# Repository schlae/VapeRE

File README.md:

# Reverse Engineered Vape Circuit Boards

Disposable vapes show up all the time in e-waste and are often found as litter at the side of the road (shame!) but they contain some useful components that can be reused by the cost-conscious hacker.

*Note: Wear gloves when handling used devices and don't allow the vape liquid to contact your skin or eyes.*

I've reverse engineered a number of different brands and placed the schematics and layout files in this repository. The summary table below is a good starting point.

Many of the vapes have debugging connections accessible through the USB-C charging cable interface, typically SWD on the CC pins, so you may be able to reprogram the vape without even opening up the case.

| Brand | PCB ID | Display | MCU | NOR flash | Battery IC | LDO regulator | Debug | Other Notes |
|-------|--------|---------|-----|-----------|------------|---------------|-------|-------------|
| (Unknown) | [FT03 V3.0](FT03/) | LCD | CHIPSEA F031K8V6 | GT 25Q32A | PC3221 | CJ6330 | SWD on CC lines. UART test points. | Touch IC TTP223. Pushbutton. 3 heater outputs with feedback. |
| Flum Mello | [TMY\_0118470101\_V04](TMY/) | LCD | CHIPSEA F031K8V6 | ZB 25VQ32 | TP4054 | CJ6330 | SWD on CC lines. | One heater output with feedback. |
| Rama 16000 | [YK761-VP9012-A](YK761/) | LCD | BlueX BX2400 or RF01 | Puya PY25Q64 | CST4056 | CJ6330 | Test points for SWD | One heater with feedback. Bluetooth (!) |
| GeekBar Pulse 15000 | [BD0027-USB\_V1.5](BD0027/) | Blue and RGB LEDs | Puya PY32F030EK28 | None | LP4068 | None | SWD on CC lines. | 3-position slide switch. Two heaters with feedback. |
| Lost Mary MO20000 Pro | [STW2915 V1.7](STW2915/) | LCD | Pya PY32F030EK28 | Puya PY32Q64 | LP4068 | CJ6330 (?) | SWD on CC lines. | |
| GeekBar Pulse X Jam | [BD0061](BD0061/) | LCD and blue LEDs, PLS916H driver IC | Puya PY32F030EK28 | None | LR5112/LR5108 | None | SWD on CC lines. | |

I also have [firmware running on the Lost Mary MO20000 Pro](STW2915/firmware) that could be modified to run on other vapes with the same PY32F030 microcontroller.

## License

All the reverse engineered hardware data is provided under the [Creative Commons Attribution-ShareAlike 4.0 International](https://creativecommons.org/licenses/by-sa/4.0/) license.

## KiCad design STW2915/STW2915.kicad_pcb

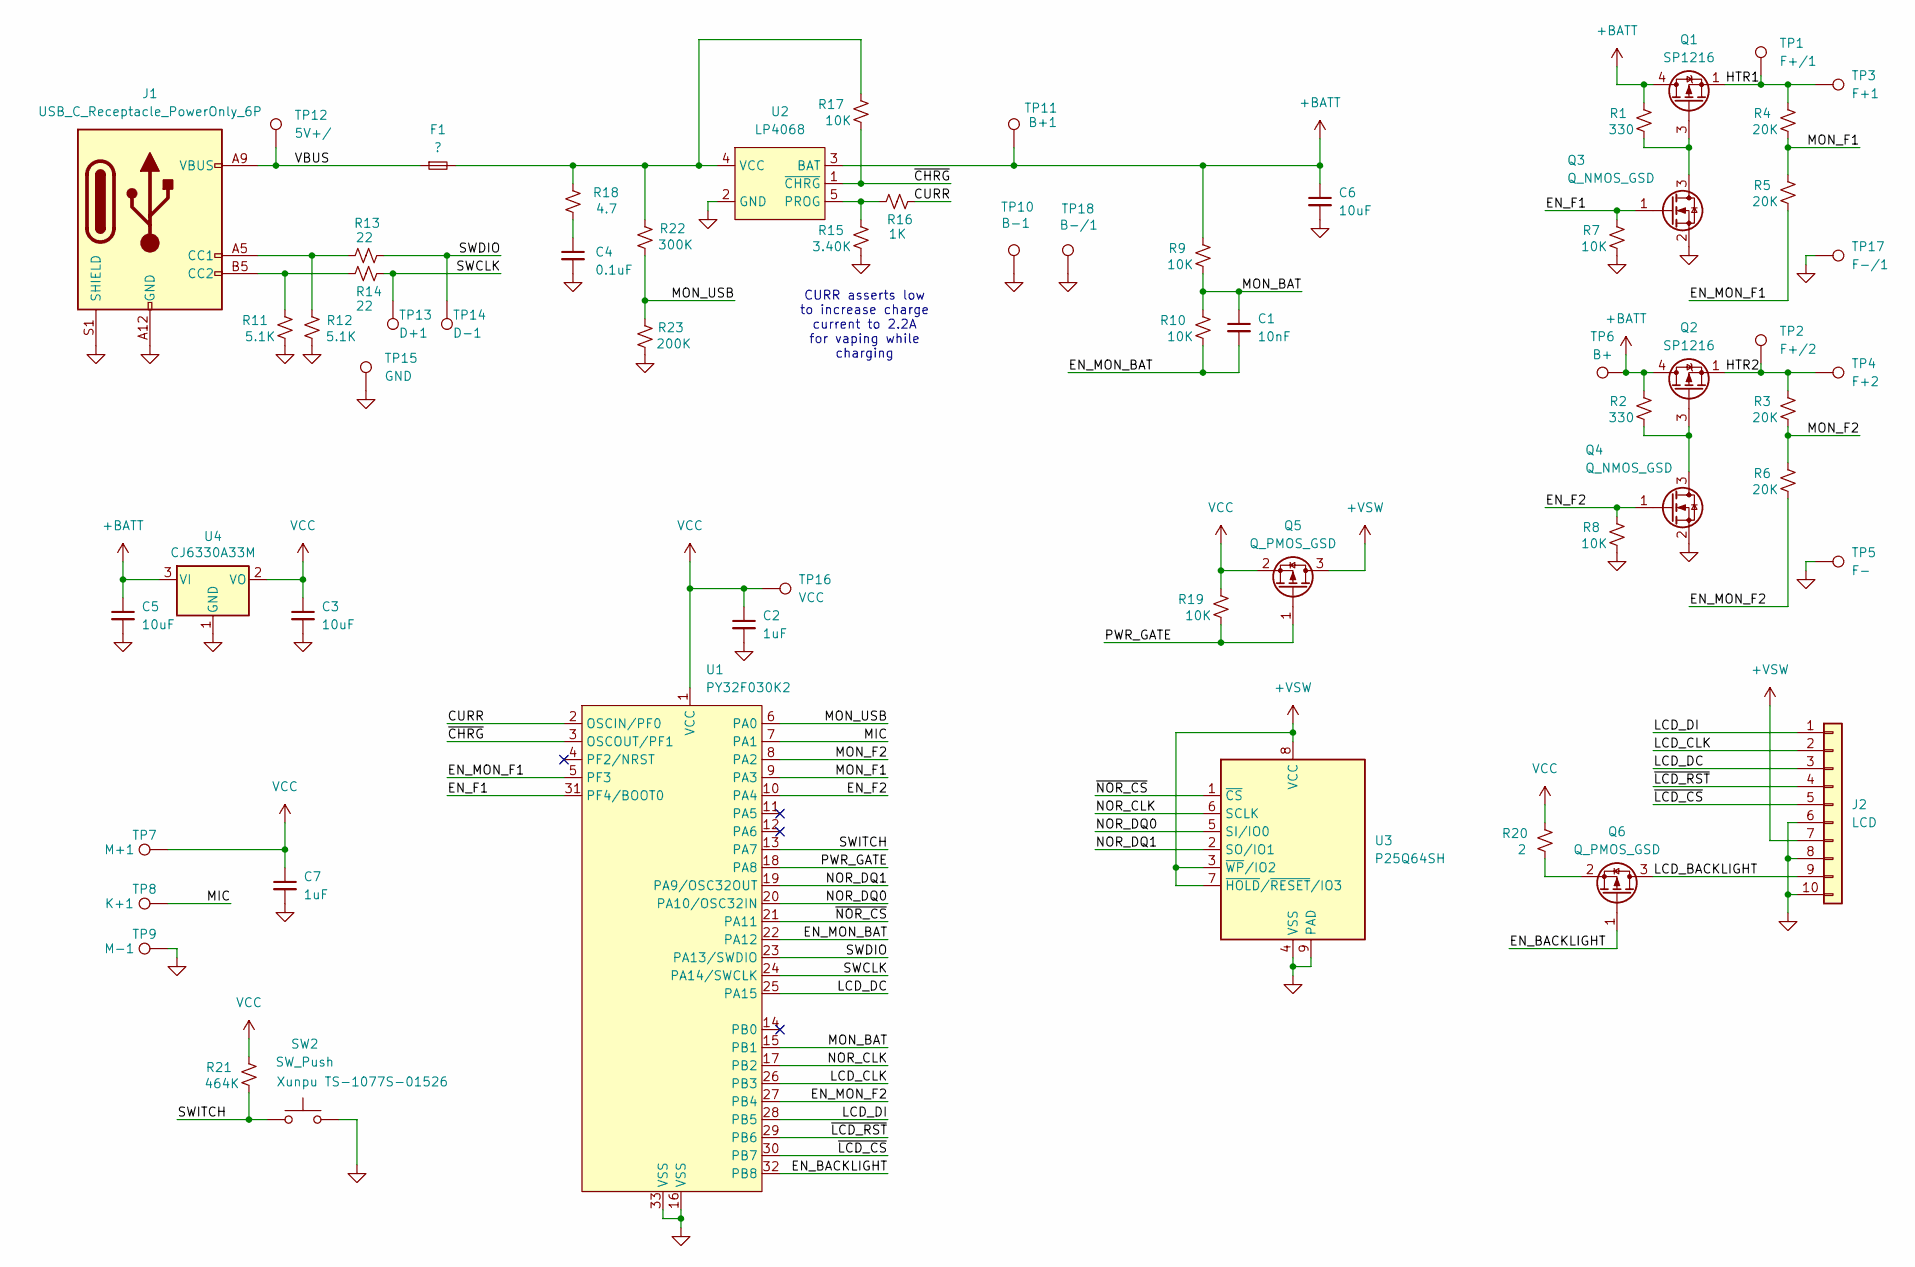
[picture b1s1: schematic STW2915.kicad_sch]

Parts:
C1: 10nF; C_0402_1005Metric
C2, C7: 1uF; C_0402_1005Metric
C3, C5, C6: 10uF; C_0402_1005Metric
C4: 0.1uF; C_0402_1005Metric
F1: ?; Fuse_0603_1608Metric
J1: USB_C_Receptacle_PowerOnly_6P; USB_C_Receptacle_TYPE-C-VERT
J2: LCD; FPC_CONN_1_2MM-10
Q1, Q2: SP1216; Texas_DQK
Q3, Q4: Q_NMOS_GSD; SOT-523
Q5, Q6: Q_PMOS_GSD; SOT-723
R1, R2: 330; R_0402_1005Metric
R3, R4, R5, R6: 20K; R_0402_1005Metric
R7, R8, R9, R10, R17, R19: 10K; R_0402_1005Metric
R11, R12: 5.1K; R_0402_1005Metric
R13, R14: 22; R_0402_1005Metric
R15: 3.40K; R_0402_1005Metric
R16: 1K; R_0402_1005Metric
R18: 4.7; R_0402_1005Metric
R20: 2; R_0402_1005Metric
R21: 464K; R_0402_1005Metric
R22: 300K; R_0402_1005Metric
R23: 200K; R_0402_1005Metric
SW2: SW_Push; SW_Push_1P1T_NO_CK_KMR2; MPN Xunpu TS-1077S-01526
TP1: F+/1; TestPoint_Pad_D1.0mm
TP2: F+/2; TestPoint_Pad_D1.0mm
TP3: F+1; TestPoint_Pad_D1.5mm
TP4: F+2; TestPoint_Pad_D1.5mm
TP5: F-; TestPoint_Pad_D1.5mm
TP6: B+; TestPoint_Pad_D1.5mm
TP7: M+1; TestPoint_Pad_D1.5mm
TP8: K+1; TestPoint_Pad_D1.5mm
TP9: M-1; TestPoint_Pad_D1.5mm
TP10: B-1; TestPoint_Pad_D1.5mm
TP11: B+1; TestPoint_Pad_D1.5mm
TP12: 5V+/; TestPoint_Pad_D1.0mm
TP13: D+1; TestPoint_Pad_D1.0mm
TP14: D-1; TestPoint_Pad_D1.0mm
TP15: GND; TestPoint_Pad_D1.0mm
TP16: VCC; TestPoint_Pad_D1.0mm
TP17: F-/1; TestPoint_Pad_D1.5mm
TP18: B-/1; TestPoint_Pad_D1.5mm
U1: PY32F030K2; QFN-32-1EP_5x5mm_P0.5mm_EP3.45x3.45mm
U2: LP4068; TSOP-5_1.65x3.05mm_P0.95mm
U3: P25Q64SH; Winbond_USON-8-1EP_3x2mm_P0.5mm_EP0.2x1.6mm
U4: CJ6330A33M; SOT95P230X117-3

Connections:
+3.3V: J2.7, Q5.3 (D), U3.3 (~WP/IO2), U3.7 (~HOLD/~RESET/IO3), U3.8 (VCC)
+BATT: C5.1, C6.1, Q1.4 (D), Q1.7 (D), Q2.4 (D), Q2.7 (D), R1.2, R2.2, R9.2, TP6.1, TP11.1, U2.3 (BAT), U4.3 (VI)
/CURR: R16.1, U1.2 (OSCIN/PF0)
/EN_BACKLIGHT: Q6.1 (G), U1.32 (PB8)
/EN_F1: Q3.1 (G), R7.2, U1.31 (PF4/BOOT0)
/EN_F2: Q4.1 (G), R8.2, U1.10 (PA4)
/EN_MON_BAT: C1.2, R10.1, U1.22 (PA12)
/EN_MON_F1: R5.1, U1.5 (PF3)
/EN_MON_F2: R6.1, U1.27 (PB4)
/HTR1: Q1.1 (S), Q1.2 (S), Q1.5 (S), Q1.6 (S), Q1.8 (S), R4.2, TP1.1, TP3.1
/HTR2: Q2.1 (S), Q2.2 (S), Q2.5 (S), Q2.6 (S), Q2.8 (S), R3.2, TP2.1, TP4.1
/LCD_BACKLIGHT: J2.9, Q6.3 (D)
/LCD_CLK: J2.2, U1.26 (PB3)
/LCD_DC: J2.3, U1.25 (PA15)
/LCD_DI: J2.1, U1.28 (PB5)
/MIC: TP8.1, U1.7 (PA1)
/MON_BAT: C1.1, R9.1, R10.2, U1.15 (PB1)
/MON_F1: R4.1, R5.2, U1.9 (PA3)
/MON_F2: R3.1, R6.2, U1.8 (PA2)
/MON_USB: R22.1, R23.2, U1.6 (PA0)
/NOR_CLK: U1.17 (PB2), U3.6 (SCLK)
/NOR_DQ0: U1.20 (PA10/OSC32IN), U3.5 (SI/IO0)
/NOR_DQ1: U1.19 (PA9/OSC32OUT), U3.2 (SO/IO1)
/PWR_GATE: Q5.1 (G), R19.1, U1.18 (PA8)
/SWCLK: R14.1, TP13.1, U1.24 (PA14/SWCLK)
/SWDIO: R13.1, TP14.1, U1.23 (PA13/SWDIO)
/SWITCH: R21.1, SW2.1, U1.13 (PA7)
/VBUS: F1.1, J1.A9 (VBUS), J1.B9 (VBUS), TP12.1
/~CHRG: R17.1, U1.3 (OSCOUT/PF1), U2.1 (~CHRG)
/~LCD_CS: J2.5, U1.30 (PB7)
/~LCD_RST: J2.4, U1.29 (PB6)
/~NOR_CS: U1.21 (PA11), U3.1 (~CS)
GND: C2.2, C3.2, C4.2, C5.2, C6.2, C7.2, J1.A12 (GND), J1.B12 (GND), J1.S1 (SHIELD), J2.6, J2.8, J2.10, Q3.2 (S), Q4.2 (S), R7.1, R8.1, R11.1, R12.1, R15.1, R23.1, SW2.2, TP5.1, TP9.1, TP10.1, TP15.1, TP17.1, TP18.1, U1.16 (VSS), U1.33 (VSS), U2.2 (GND), U3.4 (VSS), U3.9 (PAD), U4.1 (GND)
unnamed: C4.1, R18.1
unnamed: J1.A5 (CC1), R12.2, R13.2
unnamed: J1.B5 (CC2), R11.2, R14.2
unnamed: Q1.3 (G), Q3.3 (D), R1.1
unnamed: Q2.3 (G), Q4.3 (D), R2.1
unnamed: Q6.2 (S), R20.1
unnamed: R15.2, R16.2, U2.5 (PROG)
unnamed: F1.2, R17.2, R18.2, R22.2, U2.4 (VCC)
VCC: C2.1, C3.1, C7.1, Q5.2 (S), R19.2, R20.2, R21.2, TP7.1, TP16.1, U1.1 (VCC), U4.2 (VO)

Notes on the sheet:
CURR asserts low to increase charge current to 2.2A for vaping while charging

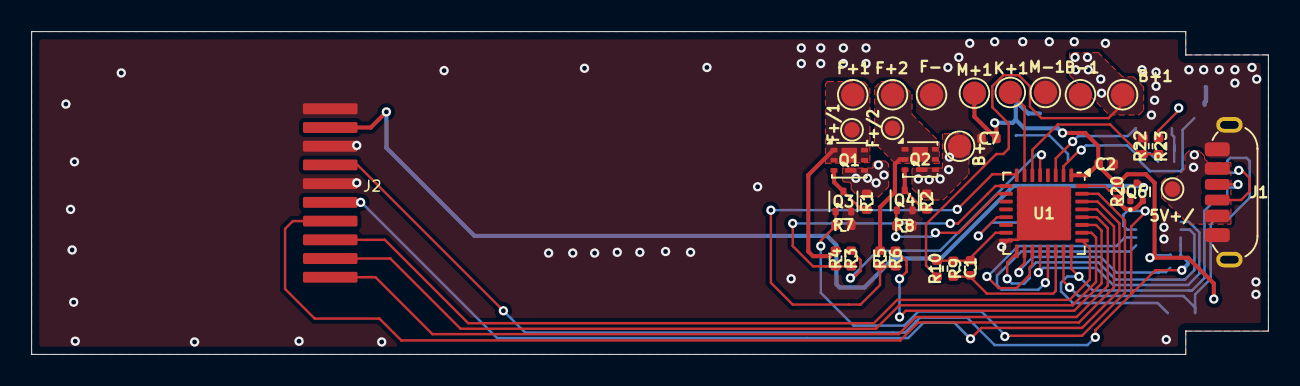
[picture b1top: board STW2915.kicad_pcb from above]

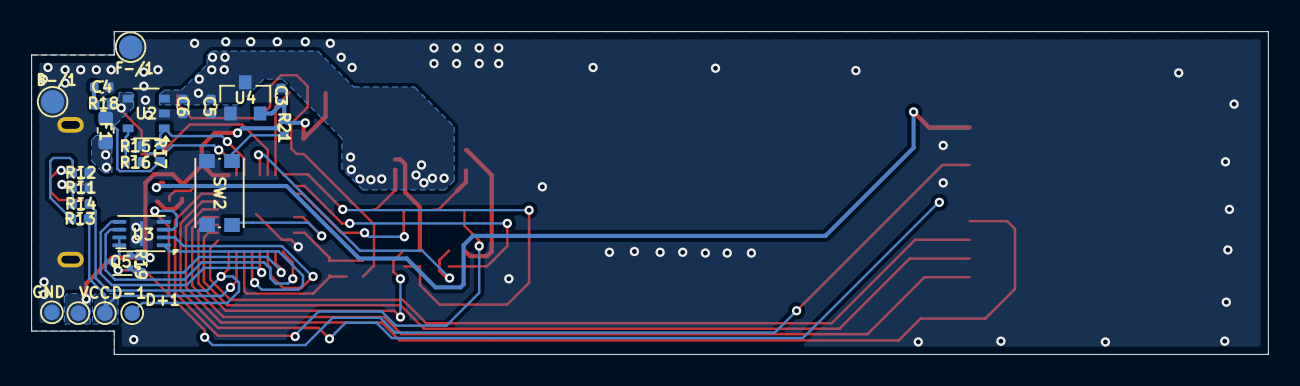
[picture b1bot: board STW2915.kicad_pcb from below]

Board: 2 copper layers, 79.3 x 20.7 mm, 62 parts (26 on the bottom side), 42 nets.

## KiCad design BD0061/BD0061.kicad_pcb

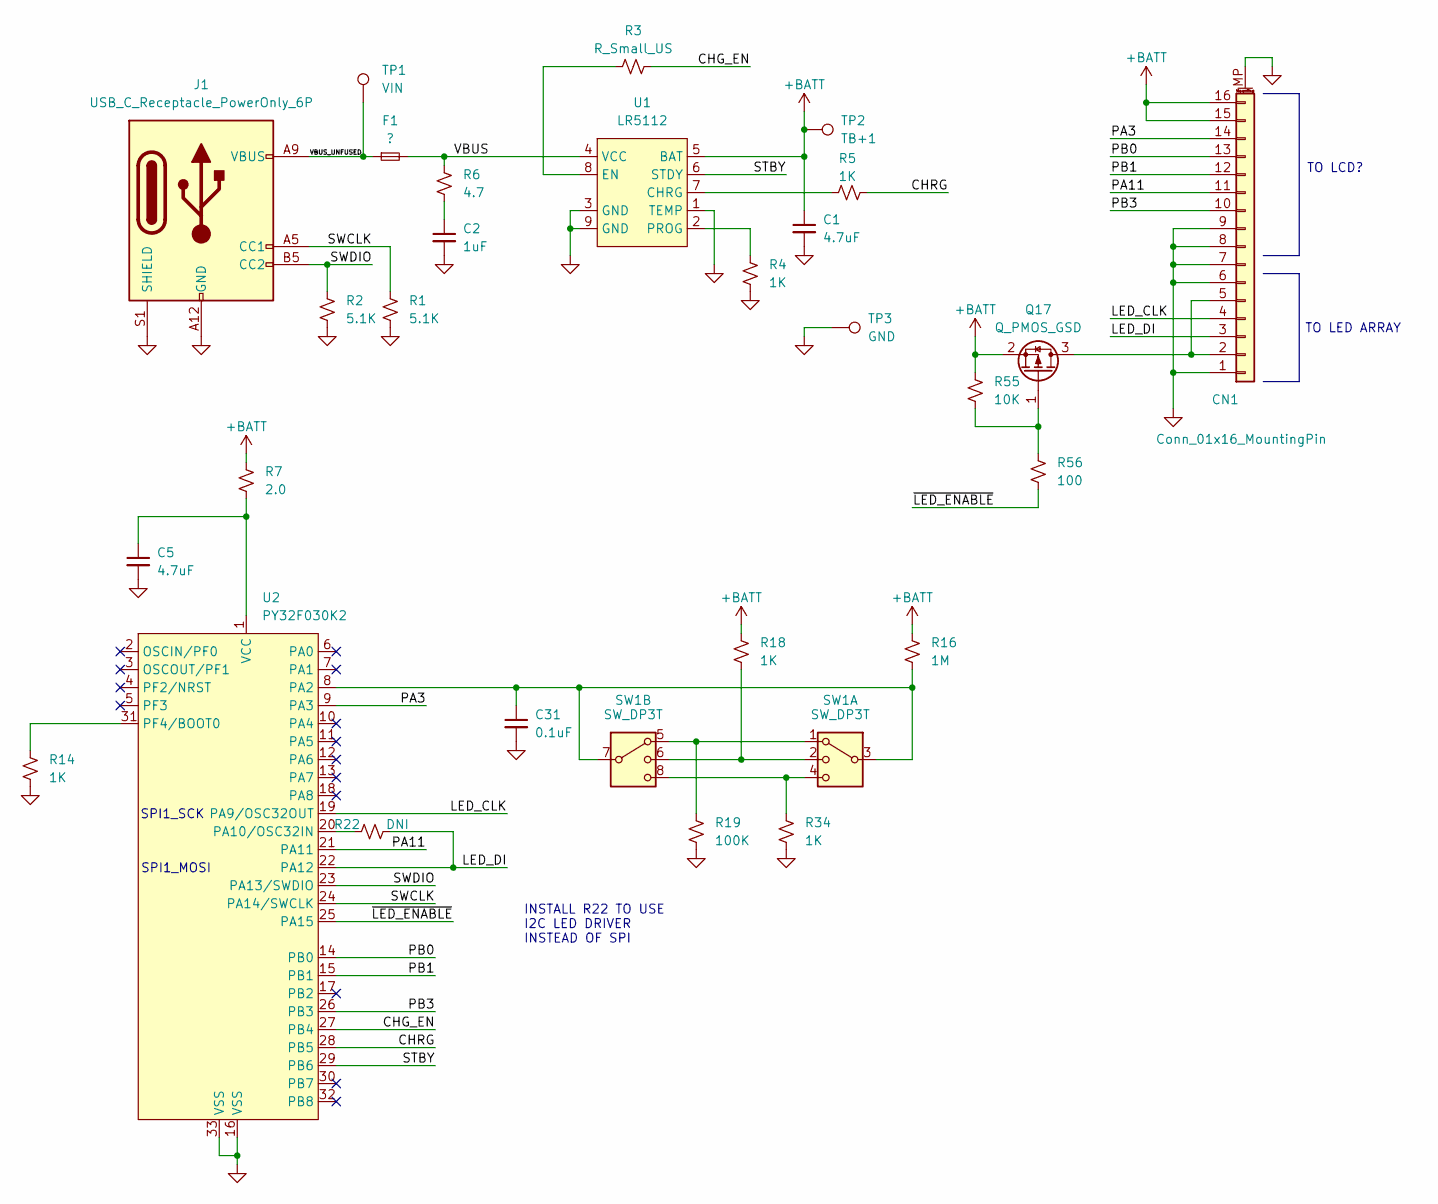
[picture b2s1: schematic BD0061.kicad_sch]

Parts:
C1: 4.7uF; C_0603_1608Metric
C2: 1uF; C_0603_1608Metric
C5: 4.7uF; C_0402_1005Metric
C31: 0.1uF; C_0402_1005Metric
CN1: Conn_01x16_MountingPin; UNK_FPC_1x16-1MP_P0.5mm_Horizontal
F1: ?; Fuse_0603_1608Metric
J1: USB_C_Receptacle_PowerOnly_6P; USB_C_Receptacle_TYPE-C-VERT
Q17: Q_PMOS_GSD; SOT-523
R1, R2: 5.1K; R_0402_1005Metric
R3: R_Small_US; R_0402_1005Metric
R4, R5, R14, R18, R34: 1K; R_0402_1005Metric
R6: 4.7; R_0402_1005Metric
R7: 2.0; R_0402_1005Metric
R16: 1M; R_0402_1005Metric
R19: 100K; R_0402_1005Metric
R22: DNI; R_0402_1005Metric
R55: 10K; R_0402_1005Metric
R56: 100; R_0402_1005Metric
SW1: SW_DP3T; SW_DP3T_SMD
TP1: VIN; TestPoint_Pad_D1.5mm
TP2: TB+1; TestPoint_Pad_D1.5mm
TP3: GND; TestPoint_Pad_D1.5mm
U1: LR5112; DFN-8-1EP_3x3mm_P0.65mm_EP1.55x2.4mm
U2: PY32F030K2; QFN-32-1EP_5x5mm_P0.5mm_EP3.45x3.45mm

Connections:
+BATT: C1.1, CN1.15, CN1.16, Q17.2 (S), R7.1, R16.2, R18.2, R55.2, TP2.1, U1.5 (BAT)
/CHG_EN: R3.2, U2.27 (PB4)
/CHRG: R5.2, U2.28 (PB5)
/PA3: CN1.14, U2.9 (PA3)
/PA9: CN1.4, U2.19 (PA9/OSC32OUT)
/PA11: CN1.11, U2.21 (PA11)
/PA12: CN1.3, R22.1, U2.22 (PA12)
/PB0: CN1.13, U2.14 (PB0)
/PB1: CN1.12, U2.15 (PB1)
/PB3: CN1.10, U2.26 (PB3)
/STBY: U1.6 (STDY), U2.29 (PB6)
/SWCLK: J1.A5 (CC1), R1.1, U2.24 (PA14/SWCLK)
/SWDIO: J1.B5 (CC2), R2.1, U2.23 (PA13/SWDIO)
/VBUS: F1.2, R6.2, U1.4 (VCC)
/VBUS_UNFUSED: F1.1, J1.A9 (VBUS), J1.B9 (VBUS), TP1.1
/~LCD_BACKLIGHT: R56.2, U2.25 (PA15)
GND: C1.2, C2.2, C5.2, C31.2, CN1.1, CN1.6, CN1.7, CN1.8, CN1.9, CN1.MP (MountPin), J1.A12 (GND), J1.B12 (GND), J1.S1 (SHIELD), R1.2, R2.2, R4.2, R14.2, R19.2, R34.2, TP3.1, U1.1 (TEMP), U1.3 (GND), U1.9 (GND), U2.16 (VSS), U2.33 (VSS)
unnamed: C2.1, R6.1
unnamed: CN1.2, CN1.5, Q17.3 (D)
unnamed: Q17.1 (G), R55.1, R56.1
unnamed: R18.1, SW1.2, SW1.6
unnamed: R19.1, SW1.1, SW1.5
unnamed: R34.1, SW1.4, SW1.8
unnamed: R5.1, U1.7 (CHRG)
unnamed: R3.1, U1.8 (EN)
unnamed: R4.1, U1.2 (PROG)
unnamed: C31.1, R16.1, SW1.3, SW1.7, U2.8 (PA2)
unnamed: R22.2, U2.20 (PA10/OSC32IN)
unnamed: R14.1, U2.31 (PF4/BOOT0)
unnamed: C5.1, R7.2, U2.1 (VCC)

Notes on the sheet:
SPI1_SCK
INSTALL R22 TO USE I2C LED DRIVER INSTEAD OF SPI
TO LED ARRAY
TO LCD?
SPI1_MOSI

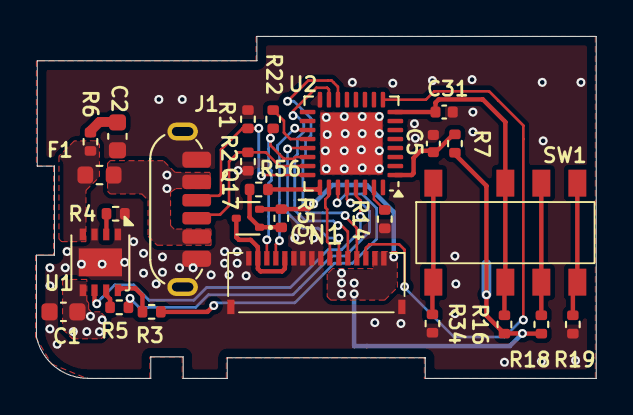
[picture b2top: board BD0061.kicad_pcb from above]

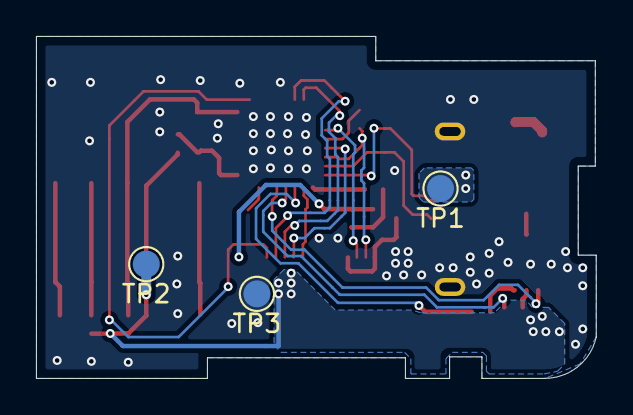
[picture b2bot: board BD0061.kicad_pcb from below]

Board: 2 copper layers, 31.1 x 19.0 mm, 29 parts (3 on the bottom side), 30 nets.

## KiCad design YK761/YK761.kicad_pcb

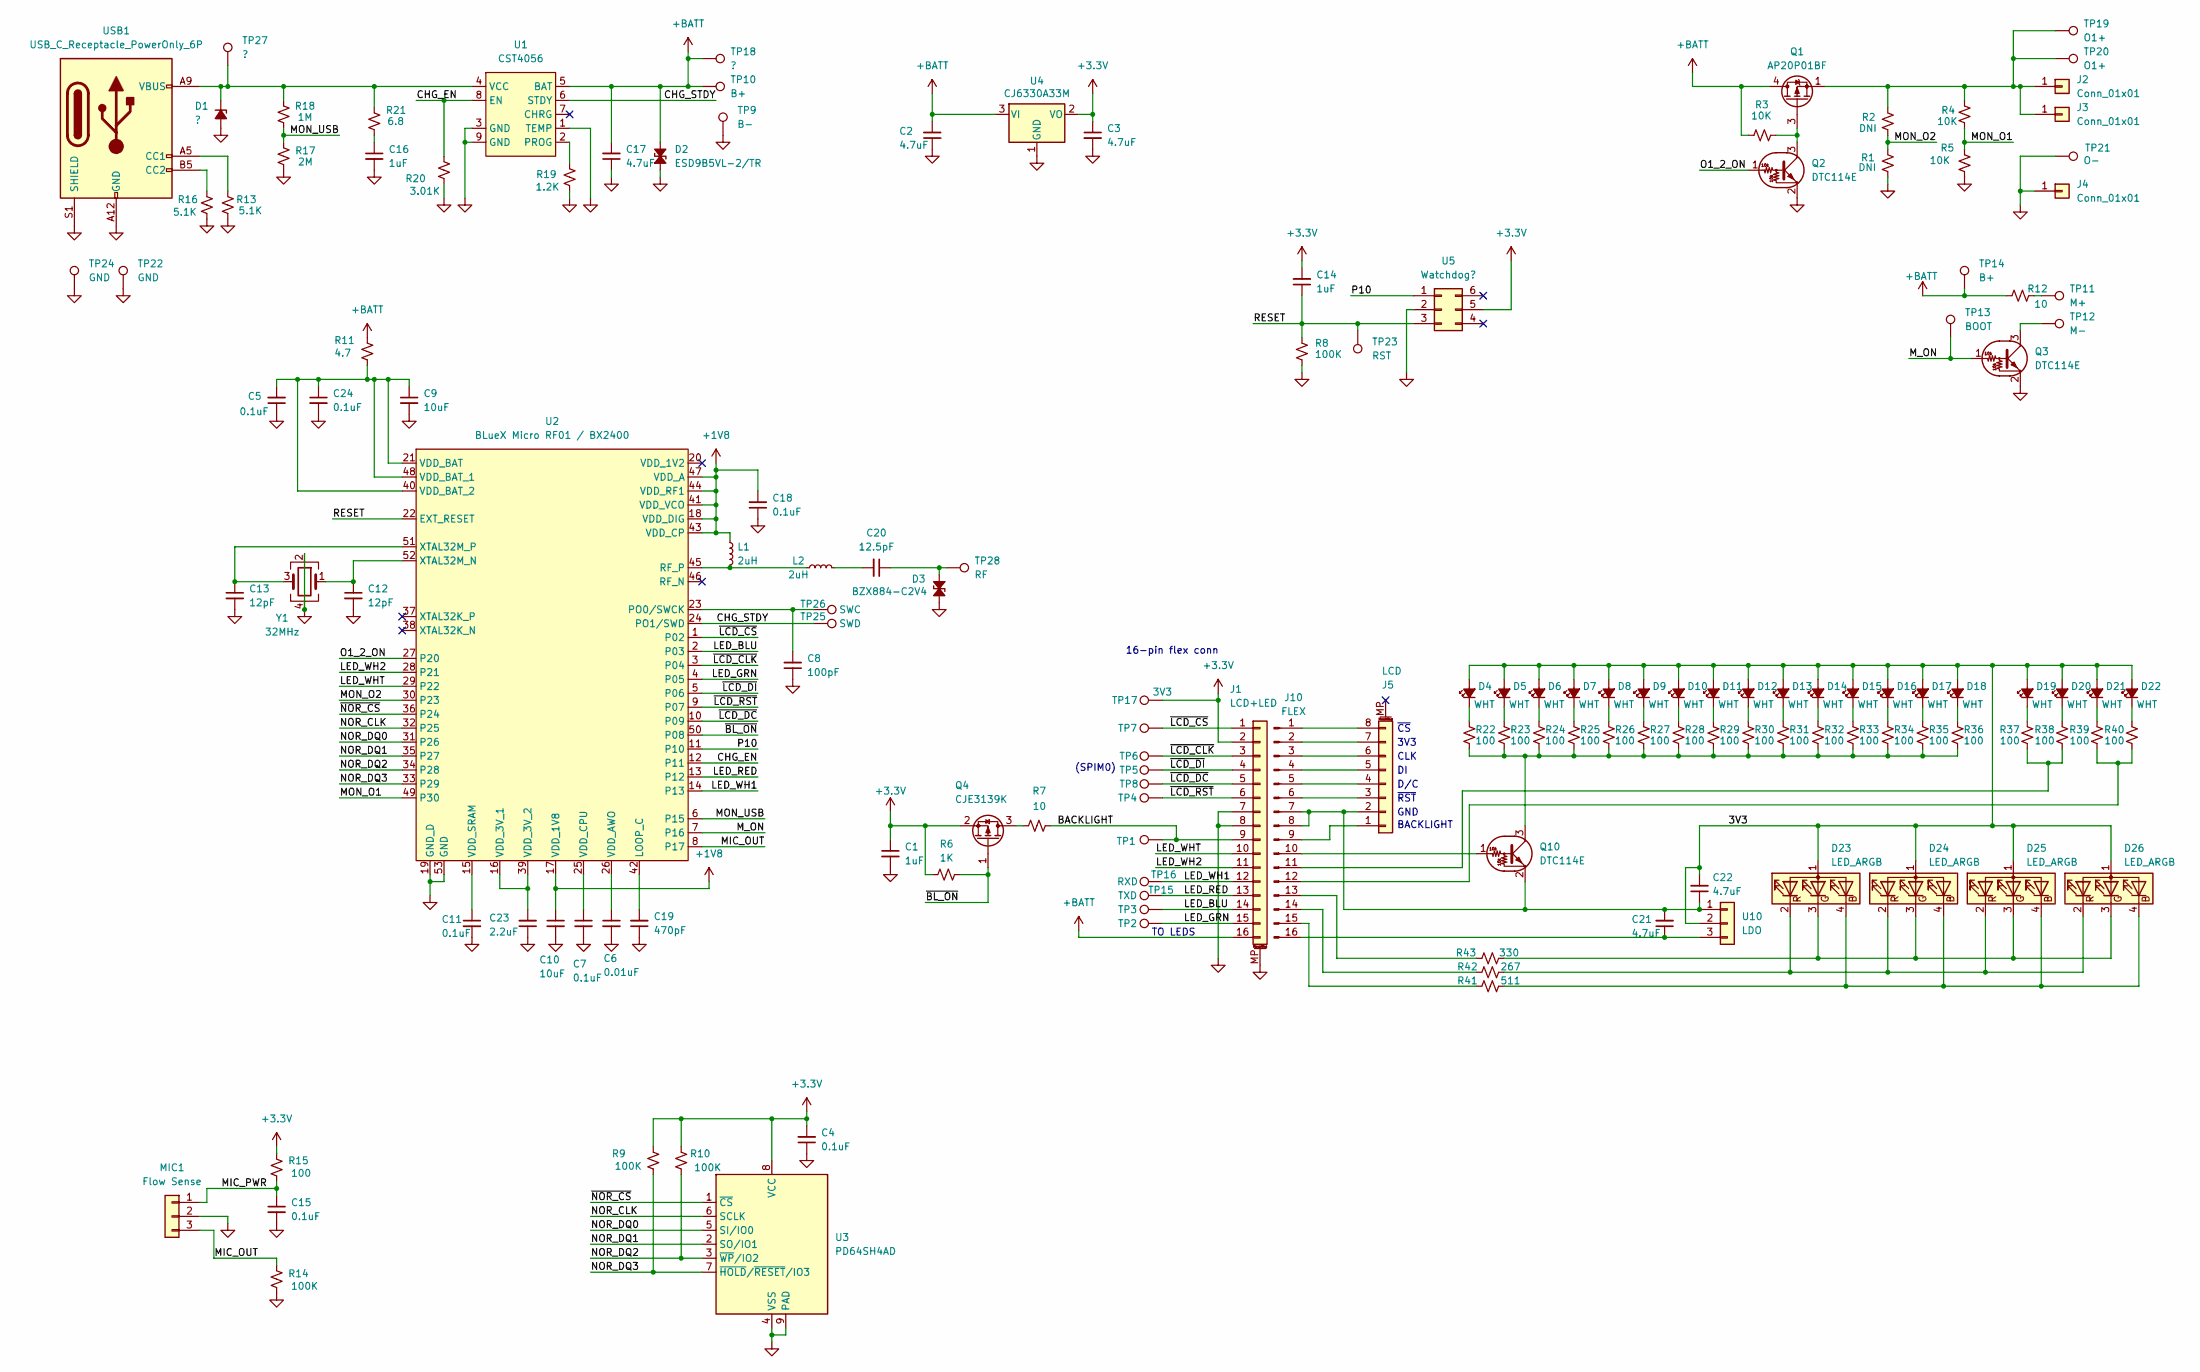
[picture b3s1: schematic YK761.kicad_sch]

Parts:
C1, C14, C16: 1uF; C_0402_1005Metric
C2, C3, C17, C21, C22: 4.7uF; C_0402_1005Metric
C4, C5, C7, C11, C15, C18, C24: 0.1uF; C_0402_1005Metric
C6: 0.01uF; C_0402_1005Metric
C8: 100pF; C_0402_1005Metric
C9, C10: 10uF; C_0402_1005Metric
C12, C13: 12pF; C_0402_1005Metric
C19: 470pF; C_0402_1005Metric
C20: 12.5pF; C_0402_1005Metric
C23: 2.2uF; C_0402_1005Metric
D1: ?; D_SOD-882
D2: ESD9B5VL-2/TR; D_SOD-882
D3: BZX884-C2V4; D_SOD-882
D4, D5, D6, D7, D8, D9, D10, D11, D12, D13, D14, D15, D16, D17, D18, D19, D20, D21, D22: WHT; LED_0603_1608Metric
D23, D24, D25, D26: LED_ARGB; LED_LiteOn_LTST-C295K_1.6x0.8mm
J1: LCD+LED; UNK_FPC_1x16-1MP_P0.5mm_Horizontal
J2, J3, J4: Conn_01x01; TestPoint_Loop_D1.80mm_Drill1.0mm_Beaded
J5: LCD; UNK_FPC_1x08-1MP_P0.5mm_Horizontal
J10: FLEX; UNK_FPC_1x16-1MP_P0.5mm_Flex
L1, L2: 2uH; L_0402_1005Metric
MIC1: Flow Sense; MIC_SMD
Q1: AP20P01BF; Texas_DQK
Q2, Q3, Q10: DTC114E; SOT-523
Q4: CJE3139K; SOT-523
R1, R2: DNI; R_0402_1005Metric
R3, R4, R5: 10K; R_0402_1005Metric
R6: 1K; R_0402_1005Metric
R7, R12: 10; R_0603_1608Metric
R8, R9, R10, R14: 100K; R_0402_1005Metric
R11: 4.7; R_0402_1005Metric
R13, R16: 5.1K; R_0402_1005Metric
R15, R22, R23, R24, R25, R26, R27, R28, R29, R30, R31, R32, R33, R34, R35, R36, R37, R38, R39, R40: 100; R_0402_1005Metric
R17: 2M; R_0402_1005Metric
R18: 1M; R_0402_1005Metric
R19: 1.2K; R_0402_1005Metric
R20: 3.01K; R_0402_1005Metric
R21: 6.8; R_0603_1608Metric
R41: 511; R_0402_1005Metric
R42: 267; R_0402_1005Metric
R43: 330; R_0402_1005Metric
TP1, TP2, TP3, TP4, TP5, TP6, TP7, TP8: TestPoint; TP1MM
TP9: B-; TestPoint_Pad_D1.5mm
TP10: B+; TestPoint_Pad_D1.5mm
TP11: M+; TP1MM
TP12: M-; TP1MM
TP13: BOOT; TP1MM
TP14: B+; TP1MM
TP15: TXD; TP1MM
TP16: RXD; TP1MM
TP17: 3V3; TP1MM
TP18, TP27: ?; TP1MM
TP19, TP20: O1+; TP1MM
TP21: O-; TP1MM
TP22, TP24: GND; TP1MM
TP23: RST; TP1MM
TP25: SWD; TP1MM
TP26: SWC; TP1MM
TP28: RF; TP1MM
U1: CST4056; DFN-8-1EP_2x2mm_P0.5mm_EP0.8x1.6mm
U2: BLueX Micro RF01 / BX2400; QFN-52_EP_6x6_Pitch0.4mm
U3: PD64SH4AD; Winbond_USON-8-1EP_3x2mm_P0.5mm_EP0.2x1.6mm
U4: CJ6330A33M; SOT95P230X117-3
U5: Watchdog?; SOT95P305X110-6
U10: LDO; SOT95P230X117-3
USB1: USB_C_Receptacle_PowerOnly_6P; USB_C_Receptacle_TYPE-C-VERT
Y1: 32MHz; Crystal_SMD_2016-4Pin_2.0x1.6mm

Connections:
+1V8: C10.1, C18.2, L1.1, U2.17 (VDD_1V8), U2.18 (VDD_DIG), U2.41 (VDD_VCO), U2.43 (VDD_CP), U2.44 (VDD_RF1), U2.47 (VDD_A)
+3.3V: C1.1, C3.1, C4.2, C14.2, J1.2, Q4.2 (S), R6.2, R9.1, R10.1, R15.1, TP17.1, U3.8 (VCC), U4.2 (VO), U5.5
+BATT: C2.2, C17.2, D2.2 (A2), J1.16, Q1.4 (D), Q1.7 (D), R3.1, R11.1, R12.1, TP10.1, TP14.1, TP18.1, U1.5 (BAT), U4.3 (VI)
/3V3: C22.2, D4.2 (A), D5.2 (A), D6.2 (A), D7.2 (A), D8.2 (A), D9.2 (A), D10.2 (A), D11.2 (A), D12.2 (A), D13.2 (A), D14.2 (A), D15.2 (A), D16.2 (A), D17.2 (A), D18.2 (A), D19.2 (A), D20.2 (A), D21.2 (A), D22.2 (A), D23.1 (A), D24.1 (A), D25.1 (A), D26.1 (A), U10.2
/BACKLIGHT: J1.9, R7.2, TP1.1
/CHG_EN: R20.2, U1.8 (EN), U2.12 (P11)
/CHG_STDY: TP25.1, U1.6 (STDY), U2.24 (PO1/SWD)
/LED_BLU: J1.14, TP3.1, U2.2 (P03)
/LED_GRN: J1.15, TP2.1, U2.4 (P05)
/LED_RED: J1.13, TP15.1, U2.13 (P12)
/LED_WH1: J1.12, TP16.1, U2.14 (P13)
/LED_WH2: J1.11, U2.28 (P21)
/LED_WHT: J1.10, U2.29 (P22)
/MIC_OUT: MIC1.3, R14.1, U2.8 (P17)
/MIC_PWR: C15.1, MIC1.1, R15.2
/MON_O1: R4.2, R5.2, U2.49 (P30)
/MON_O2: R1.2, R2.2, U2.30 (P23)
/MON_USB: R17.1, R18.1, U2.6 (P15)
/M_ON: Q3.1 (B), TP13.1, U2.7 (P16)
/NOR_CLK: U2.32 (P25), U3.6 (SCLK)
/NOR_DQ0: U2.31 (P26), U3.5 (SI/IO0)
/NOR_DQ1: U2.35 (P27), U3.2 (SO/IO1)
/NOR_DQ2: R10.2, U2.34 (P28), U3.3 (~WP/IO2)
/NOR_DQ3: R9.2, U2.33 (P29), U3.7 (~HOLD/~RESET/IO3)
/O1_2_ON: Q2.1 (B), U2.27 (P20)
/P10: U2.11 (P10), U5.1
/RESET: C14.1, R8.1, TP23.1, U2.22 (EXT_RESET), U5.3
/~BL_ON: Q4.1 (G), R6.1, U2.50 (P08)
/~LCD_CLK: J1.3, TP6.1, U2.3 (P04)
/~LCD_CS: J1.1, TP7.1, U2.1 (P02)
/~LCD_DC: J1.5, TP8.1, U2.10 (P09)
/~LCD_DI: J1.4, TP5.1, U2.5 (P06)
/~LCD_RST: J1.6, TP4.1, U2.9 (P07)
/~NOR_CS: U2.36 (P24), U3.1 (~CS)
GND: C1.2, C2.1, C3.2, C4.1, C5.1, C6.2, C7.2, C8.1, C9.2, C10.2, C11.2, C12.2, C13.2, C15.2, C16.2, C17.1, C18.1, C19.1, C23.1, C24.2, D1.2 (A), D2.1 (A1), D3.2 (A2), J1.7, J1.8, J1.MP (MountPin), J4.1, MIC1.2, Q2.2 (E), Q3.2 (E), R1.1, R5.1, R8.2, R13.1, R14.2, R16.1, R17.2, R19.1, R20.1, TP9.1, TP21.1, TP22.1, TP24.1, U1.1 (TEMP), U1.3 (GND), U1.9 (GND), U2.19 (GND_D), U2.53 (GND), U3.4 (VSS), U3.9 (PAD), U4.1 (GND), U5.2, USB1.A12 (GND), USB1.B12 (GND), USB1.S1 (SHIELD), Y1.2, Y1.4
unnamed: C16.1, R21.2
unnamed: C20.2, L2.2
unnamed: D1.1 (K), R18.2, R21.1, TP27.1, U1.4 (VCC), USB1.A9 (VBUS), USB1.B9 (VBUS)
unnamed: C20.1, D3.1 (A1), TP28.1
unnamed: D4.1 (K), R22.1
unnamed: D5.1 (K), R23.1
unnamed: D6.1 (K), R24.1
unnamed: D7.1 (K), R25.1
unnamed: D8.1 (K), R26.1
unnamed: D9.1 (K), R27.1
unnamed: D10.1 (K), R28.1
unnamed: D11.1 (K), R29.1
unnamed: D12.1 (K), R30.1
unnamed: D13.1 (K), R31.1
unnamed: D14.1 (K), R32.1
unnamed: D15.1 (K), R33.1
unnamed: D16.1 (K), R34.1
unnamed: D17.1 (K), R35.1
unnamed: D18.1 (K), R36.1
unnamed: D19.1 (K), R37.2
unnamed: D20.1 (K), R38.2
unnamed: D21.1 (K), R39.2
unnamed: D22.1 (K), R40.2
unnamed: D23.4 (BK), D24.4 (BK), D25.4 (BK), D26.4 (BK), R41.1
unnamed: D23.3 (GK), D24.3 (GK), D25.3 (GK), D26.3 (GK), R43.1
unnamed: D23.2 (RK), D24.2 (RK), D25.2 (RK), D26.2 (RK), R42.1
unnamed: J2.1, J3.1, Q1.1 (S), Q1.2 (S), Q1.5 (S), Q1.6 (S), Q1.8 (S), R2.1, R4.1, TP19.1, TP20.1
unnamed: J5.8, J10.1
unnamed: J5.7, J10.2
unnamed: J5.6, J10.3
unnamed: J5.5, J10.4
unnamed: J5.4, J10.5
unnamed: J5.3, J10.6
unnamed: C21.2, C22.1, J5.2, J10.7, J10.8, Q10.2 (E), U10.1
unnamed: J5.1, J10.9
unnamed: J10.10, Q10.1 (B)
unnamed: J10.11, R37.1, R38.1
unnamed: J10.12, R39.1, R40.1
unnamed: J10.13, R43.2
unnamed: J10.14, R42.2
unnamed: J10.15, R41.2
unnamed: C21.1, J10.16, U10.3
unnamed: Q1.3 (G), Q2.3 (C), R3.2
unnamed: Q3.3 (C), TP12.1
unnamed: Q4.3 (D), R7.1
unnamed: Q10.3 (C), R22.2, R23.2, R24.2, R25.2, R26.2, R27.2, R28.2, R29.2, R30.2, R31.2, R32.2, R33.2, R34.2, R35.2, R36.2
unnamed: R12.2, TP11.1
unnamed: R19.2, U1.2 (PROG)
unnamed: C19.2, U2.42 (LOOP_C)
unnamed: C8.2, TP26.1, U2.23 (PO0/SWCK)
unnamed: L1.2, L2.1, U2.45 (RF_P)
unnamed: C23.2, U2.16 (VDD_3V_1), U2.39 (VDD_3V_2)
unnamed: C6.1, U2.26 (VDD_AWO)
unnamed: C5.2, C9.1, C24.1, R11.2, U2.21 (VDD_BAT), U2.40 (VDD_BAT_2), U2.48 (VDD_BAT_1)
unnamed: C7.1, U2.25 (VDD_CPU)
unnamed: C11.1, U2.15 (VDD_SRAM)
unnamed: C12.1, U2.52 (XTAL32M_N), Y1.1
unnamed: C13.1, U2.51 (XTAL32M_P), Y1.3
unnamed: R13.2, USB1.A5 (CC1)
unnamed: R16.2, USB1.B5 (CC2)

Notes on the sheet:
(SPIM0)
BACKLIGHT
~{CS}
3V3
~{RST}
16-pin flex conn
TO LEDS
CLK
GND
D/C

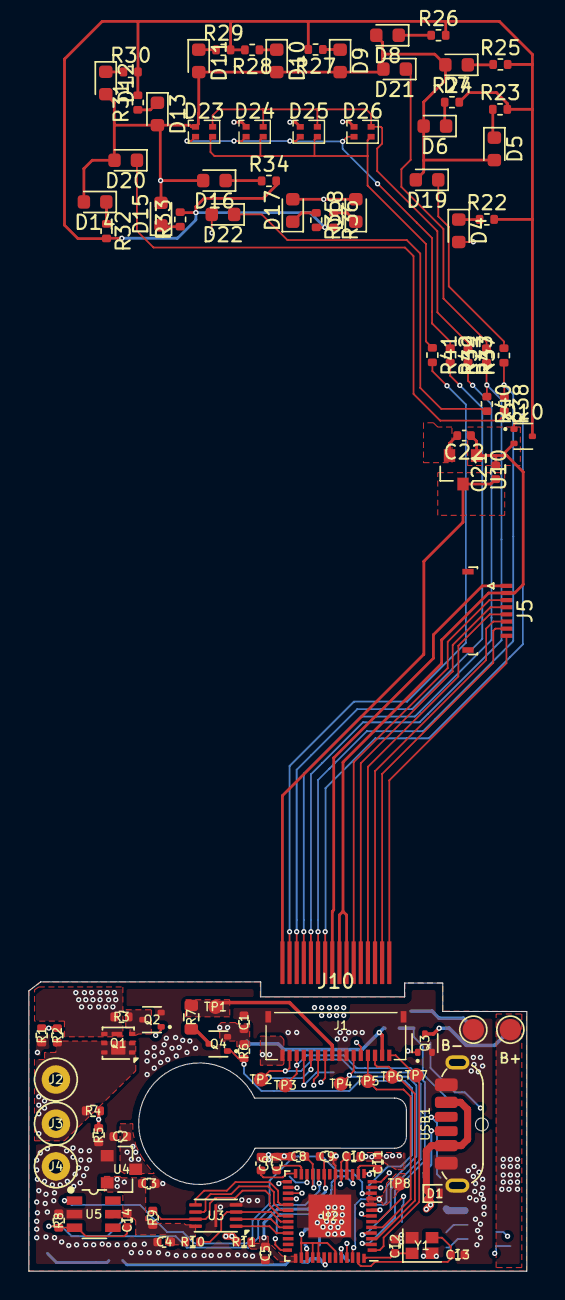
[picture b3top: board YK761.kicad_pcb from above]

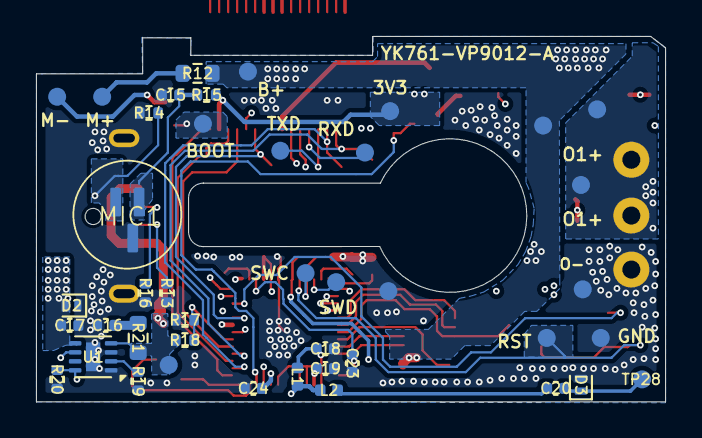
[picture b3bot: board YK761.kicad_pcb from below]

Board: 4 copper layers, 34.9 x 20.3 mm, 143 parts (42 on the bottom side), 95 nets.
